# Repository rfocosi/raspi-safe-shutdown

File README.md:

# raspi-safe-shutdown
Hardware and software project for a safe shutdown system on Raspberry Pi

sudo dtc -I dts -O dtb -o /boot/dt-blob.bin dt-blob.dts

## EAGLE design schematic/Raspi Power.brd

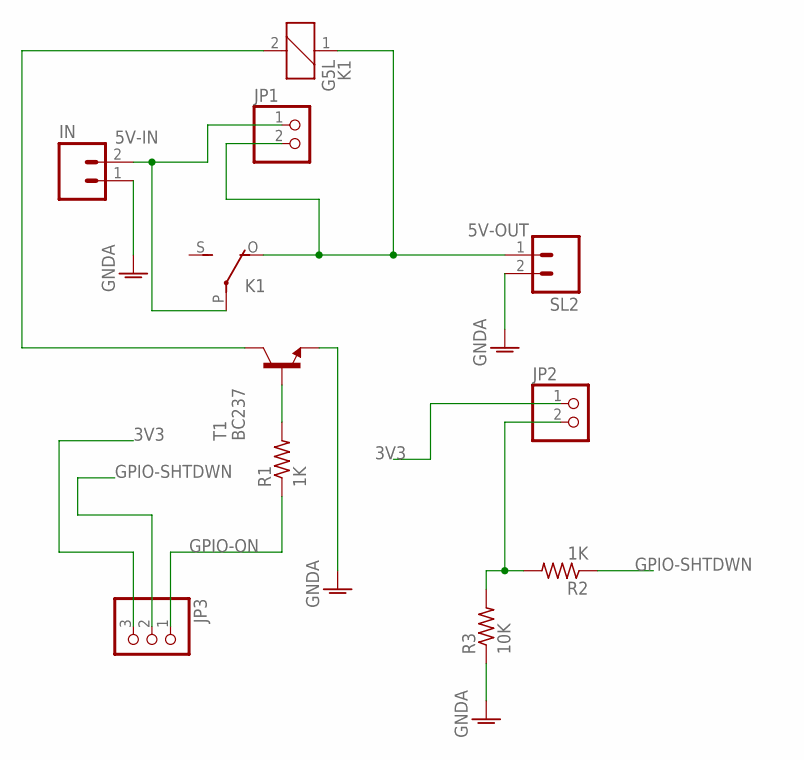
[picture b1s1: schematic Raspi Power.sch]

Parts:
IN: M02; 02P
JP1, JP2: PINHD-1X2; 1X02
JP3: PINHD-1X3; 1X03
K1: G5L; G5LE
R1, R2: 1K; 0204/7
R3: 10K; 0204/7
SL2: M02; 02P
T1: BC237; TO92

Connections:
3V3: JP2.1, JP3.3
5V-IN: IN.2, JP1.1, K1.P
5V-OUT: JP1.2, K1.1, K1.O, SL2.1
B: R1.2, T1.2 (B)
GNDA: IN.1, R3.1, SL2.2, T1.1 (E)
GPIO-ON: JP3.1, R1.1
GPIO-SHTDWN: JP3.2, R2.1
unnamed: K1.2, T1.3 (C)
unnamed: JP2.2, R2.2, R3.2

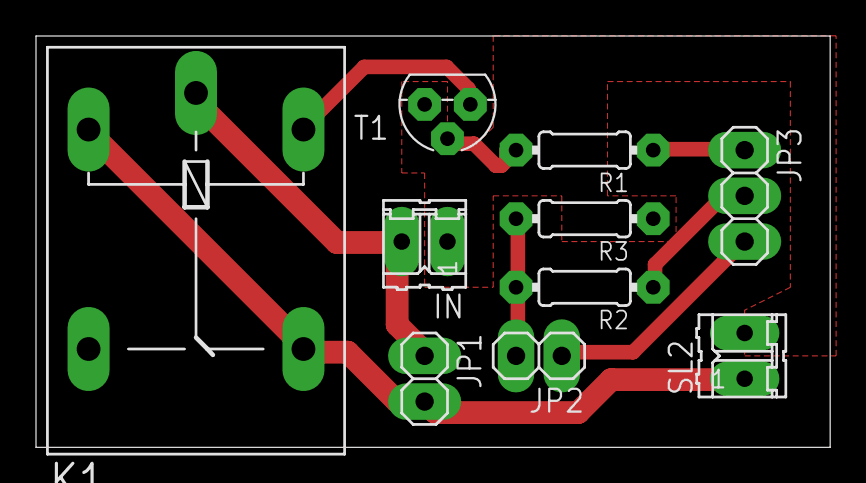
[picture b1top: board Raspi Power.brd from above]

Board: 2 copper layers, 44.1 x 22.9 mm, 10 parts (0 on the bottom side), 9 nets.

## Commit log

2017-06-03 Added EAGLE schematic
2017-06-03 Updated Schematic and configured gitignore
2017-06-03 Fixed initial schematic
2017-06-04 Added binary dt-blob
2020-04-12 New board design
